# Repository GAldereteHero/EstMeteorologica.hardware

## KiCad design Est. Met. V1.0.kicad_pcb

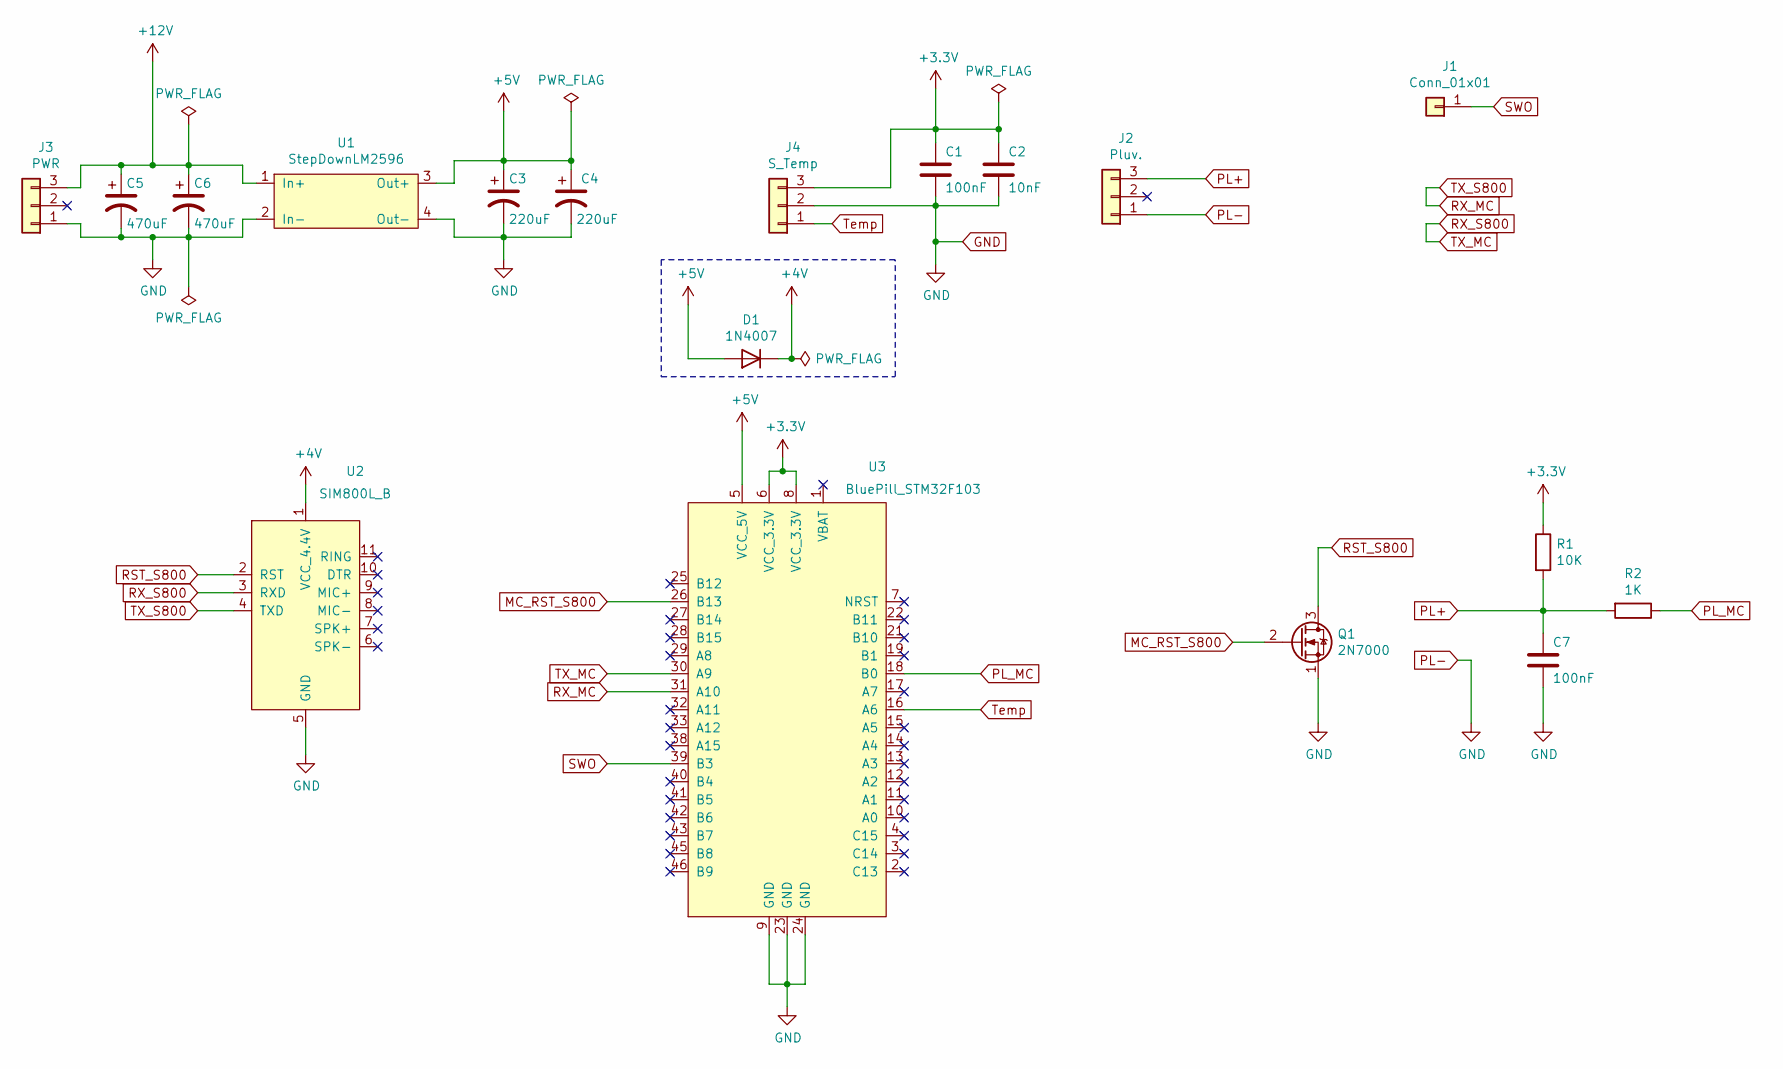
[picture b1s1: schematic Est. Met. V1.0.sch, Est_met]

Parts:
C1, C7: 100nF; C_1206_0805_Dual
C2: 10nF; C_1206_0805_Dual
C3, C4: 220uF; CP_Radial_D8.0mm_P3.80mm
C5, C6: 470uF; CP_Radial_D8.0mm_P3.80mm
D1: 1N4007; D_DO-41_SOD81_P10.16mm_Horizontal
J1: Conn_01x01; PinHeader_1x01_P2.54mm_Vertical
J2: Pluv.; PinHeader_1x03_P2.54mm_Vertical
J3: PWR; PinHeader_1x03_P2.54mm_Vertical
J4: S_Temp; PinHeader_1x03_P2.54mm_Vertical
Q1: 2N7000; TO_92_HandSolder
R1: 10K; R_1206_0805_Dual
R2: 1K; R_1206_0805_Dual
U1: StepDownLM2596
U2: SIM800L_B; SIM800_B
U3: BluePill_STM32F103

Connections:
+3V3: C1.1, C2.1, J4.3, R1.1, U3.6 (VCC_3.3V), U3.8 (VCC_3.3V)
+4V: D1.1 (K), U2.1 (VCC_4.4V)
+5V: C3.1, C4.1, D1.2 (A), U1.3 (Out+), U3.5 (VCC_5V)
+12V: C5.1, C6.1, J3.3, U1.1 (In+)
GND: C1.2, C2.2, C3.2, C4.2, C5.2, C6.2, C7.2, J2.1, J3.1, J4.2, Q1.1 (S), U1.2 (In-), U1.4 (Out-), U2.5 (GND), U3.9 (GND), U3.23 (GND), U3.24 (GND)
MC_RST_S800: Q1.2 (G), U3.26 (B13)
PL+: C7.1, J2.3, R1.2, R2.2
PL_MC: R2.1, U3.18 (B0)
RST_S800: Q1.3 (D), U2.2 (RST)
RX_MC: U2.4 (TXD), U3.31 (A10)
RX_S800: U2.3 (RXD), U3.30 (A9)
SWO: J1.1, U3.39 (B3)
Temp: J4.1, U3.16 (A6)

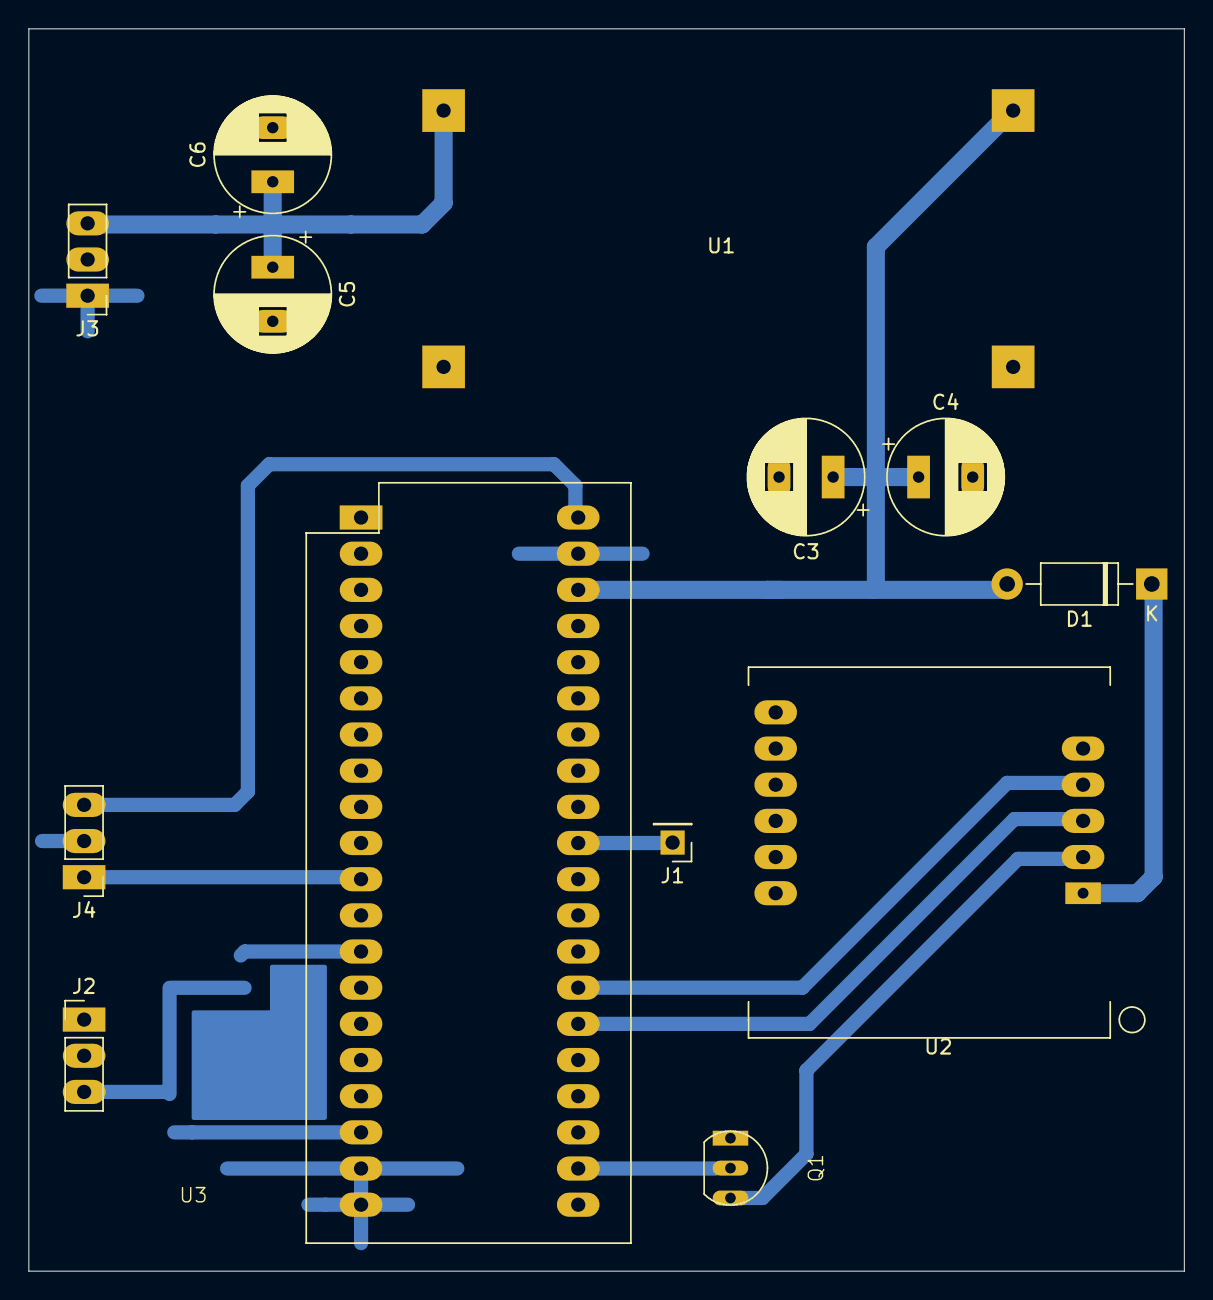
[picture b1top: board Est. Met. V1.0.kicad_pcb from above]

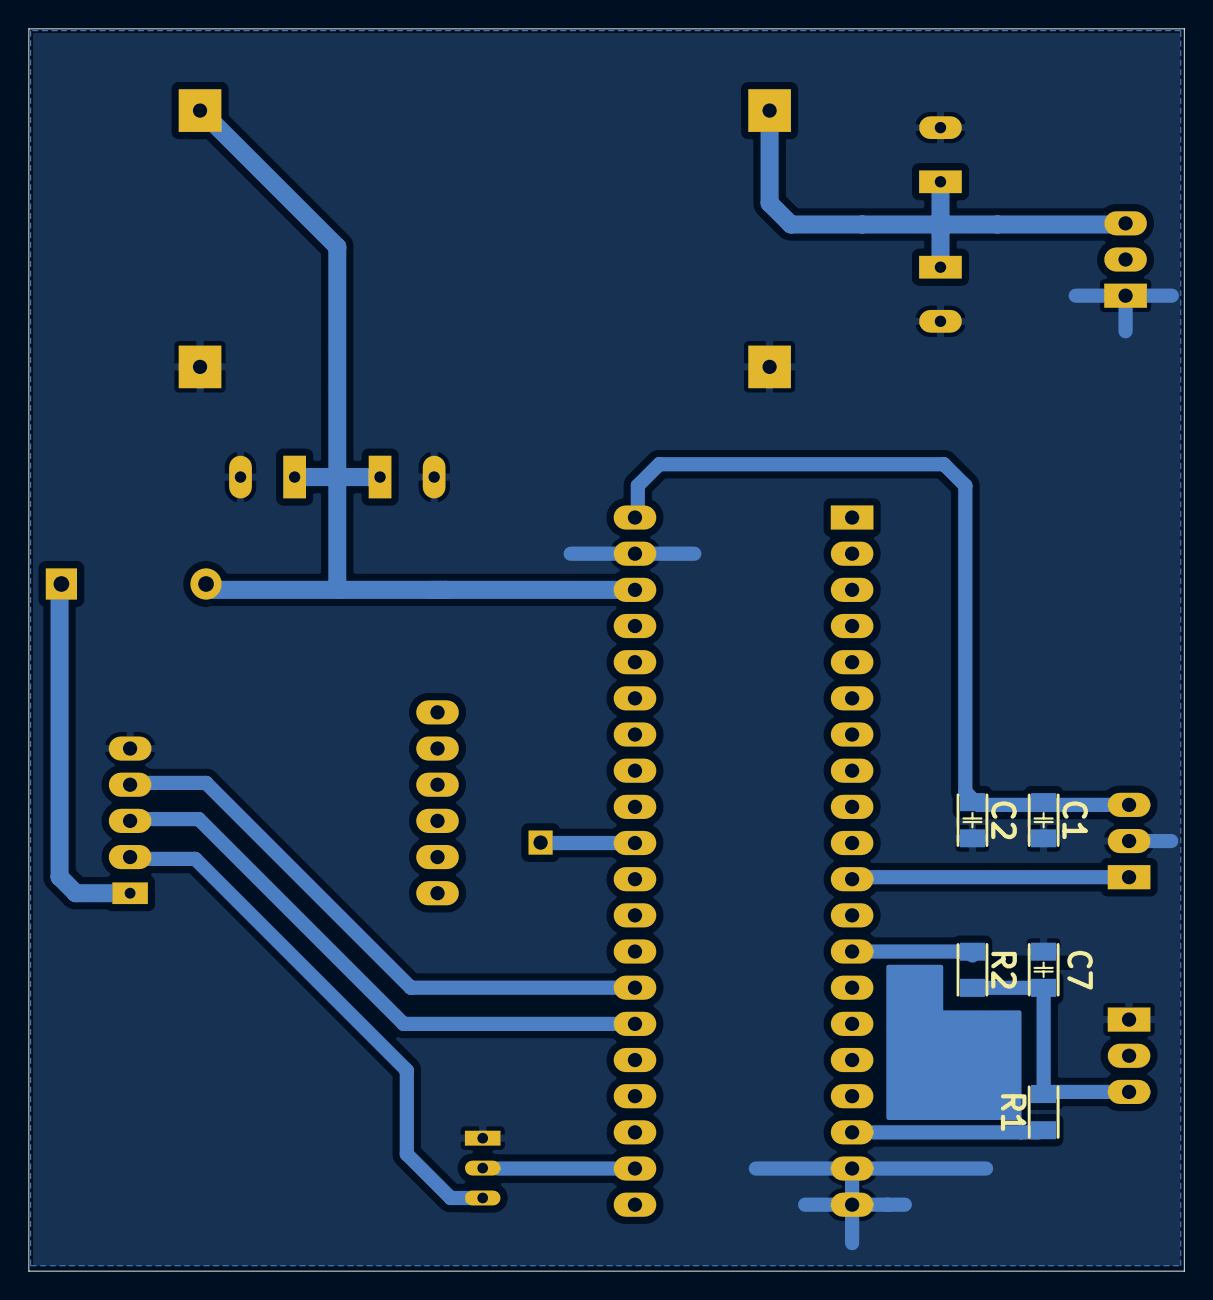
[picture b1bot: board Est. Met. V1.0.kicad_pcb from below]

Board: 2 copper layers, 81.2 x 87.2 mm, 18 parts (5 on the bottom side), 13 nets.

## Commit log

2022-01-19 Commit inicial del PCB diseñado para la est. metereologica. Diseño para montar modulos.
2022-01-28 Routeo con el modulo SIM800L
2022-02-17 Nueva placa
2022-02-25 Modificaciones del plano de masa para optimizar el proceso de fab. de la CNC.
